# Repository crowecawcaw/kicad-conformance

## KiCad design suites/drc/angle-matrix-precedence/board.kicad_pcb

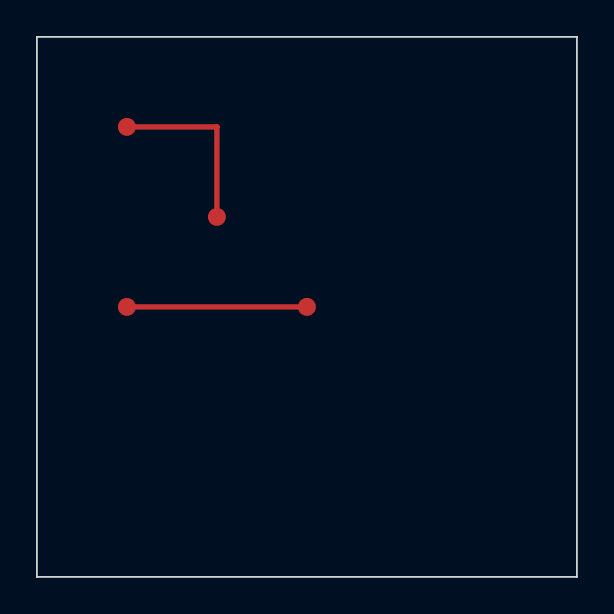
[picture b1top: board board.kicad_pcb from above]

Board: 2 copper layers, 30.0 x 30.0 mm, 4 parts (0 on the bottom side), 2 nets.

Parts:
ANGLE_BEND_A: Test
ANGLE_BEND_B: Test
ANGLE_STRAIGHT_A: Test
ANGLE_STRAIGHT_B: Test

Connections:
ANGLE_BEND: ANGLE_BEND_A.1, ANGLE_BEND_B.1
ANGLE_STRAIGHT: ANGLE_STRAIGHT_A.1, ANGLE_STRAIGHT_B.1
